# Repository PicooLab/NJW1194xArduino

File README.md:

# NJW1194 x Arduino

2-Channel Electronic Volume With Input Selector And Tone Control

Designed with Kicad and Arduino IDE;

## Related

+ NJW1194
  <https://www.njr.com/semicon/products/NJW1194.html>
  [Datasheet](assets/NJW1194_E.pdf)
+ Arduino Nano
  <https://store.arduino.cc/usa/arduino-nano>
+ 1602_I2C Screen
  <https://github.com/mathertel/LiquidCrystal_PCF8574>
+ EC11 Ratary Encoder
  <https://tech.alpsalpine.com/prod/e/html/encoder/incremental/ec11/ec11_list.html>

## Hardware

### 1. NJW1194 board

Size : 60mmx60mm

### 2. POWER board

Size : 60mmx60mm

### 3. CONTROL board

Size : 36mmx50mm

## Software

[Arduino nano](nano_eeprom_bal/nano_eeprom_bal.ino)

not elegant enough yet

## Assemble

TBD...

## MIT License

Copyright (c) 2020 ATRiiX

Permission is hereby granted, free of charge, to any person obtaining a copy
of this software and associated documentation files (the "Software"), to deal
in the Software without restriction, including without limitation the rights
to use, copy, modify, merge, publish, distribute, sublicense, and/or sell
copies of the Software, and to permit persons to whom the Software is
furnished to do so, subject to the following conditions:

The above copyright notice and this permission notice shall be included in all
copies or substantial portions of the Software.

THE SOFTWARE IS PROVIDED "AS IS", WITHOUT WARRANTY OF ANY KIND, EXPRESS OR
IMPLIED, INCLUDING BUT NOT LIMITED TO THE WARRANTIES OF MERCHANTABILITY,
FITNESS FOR A PARTICULAR PURPOSE AND NONINFRINGEMENT. IN NO EVENT SHALL THE
AUTHORS OR COPYRIGHT HOLDERS BE LIABLE FOR ANY CLAIM, DAMAGES OR OTHER
LIABILITY, WHETHER IN AN ACTION OF CONTRACT, TORT OR OTHERWISE, ARISING FROM,
OUT OF OR IN CONNECTION WITH THE SOFTWARE OR THE USE OR OTHER DEALINGS IN THE
SOFTWARE.

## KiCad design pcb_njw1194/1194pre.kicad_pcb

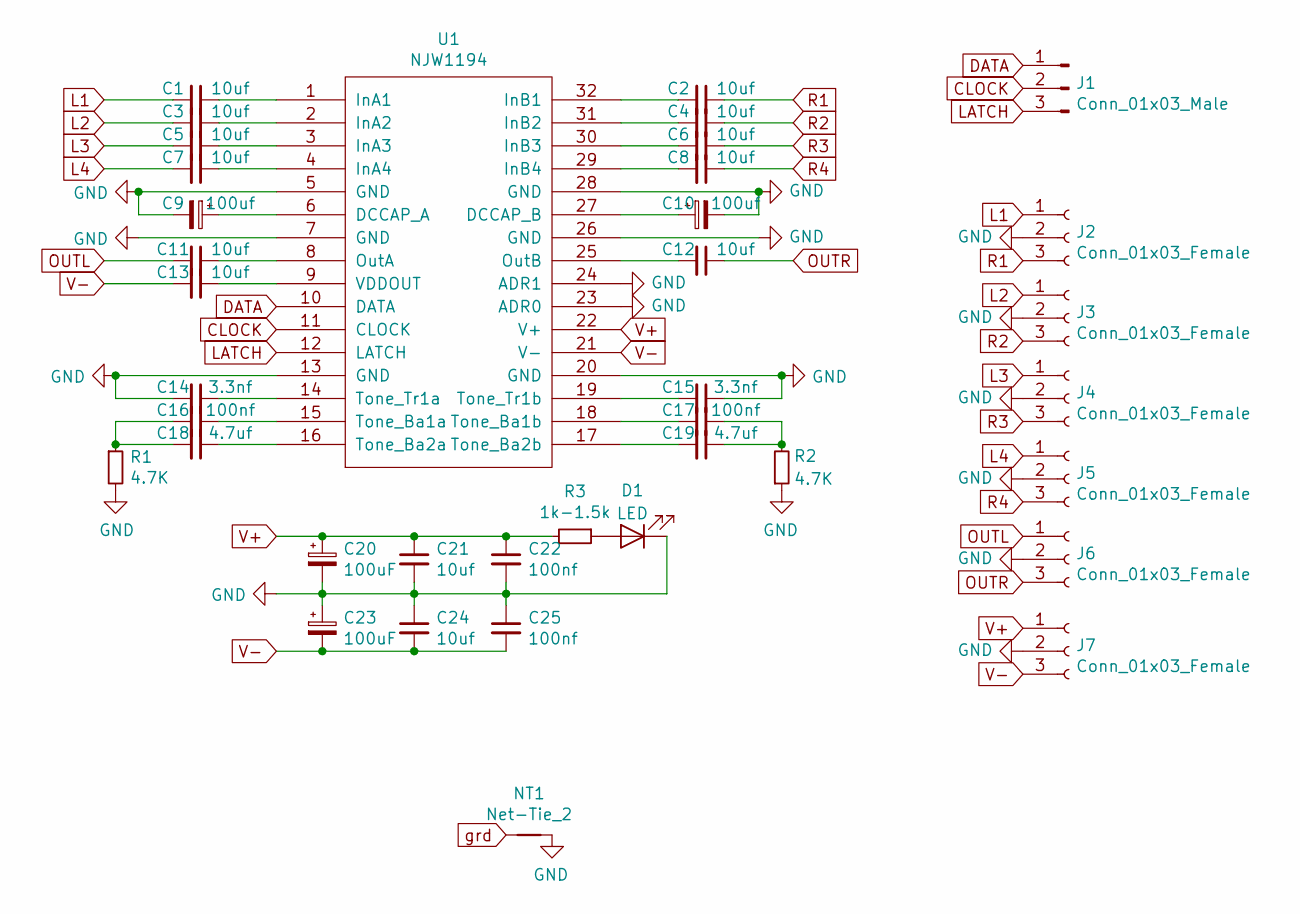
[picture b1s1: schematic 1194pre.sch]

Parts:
C1, C2, C3, C4, C5, C6, C7, C8, C11, C12, C13, C21, C24: 10uf; C_0805_2012Metric_Pad1.15x1.40mm_HandSolder
C9, C10: 100uf; CP_Radial_D8.0mm_P3.50mm
C14, C15: 3.3nf; C_0805_2012Metric_Pad1.15x1.40mm_HandSolder
C16, C17, C22, C25: 100nf; C_0603_1608Metric_Pad1.05x0.95mm_HandSolder
C18, C19: 4.7uf; C_0805_2012Metric_Pad1.15x1.40mm_HandSolder
C20, C23: 100uF; CP_Radial_D8.0mm_P3.50mm
D1: LED; LED_D3.0mm
J1: Conn_01x03_Male; PinHeader_1x03_P2.54mm_Vertical
J2, J3, J4, J5, J6, J7: Conn_01x03_Female; JST_XH_B3B-XH-A_1x03_P2.50mm_Vertical
NT1: Net-Tie_2; NetTie-2_SMD_Pad2.0mm
R1, R2: 4.7K; R_0805_2012Metric_Pad1.15x1.40mm_HandSolder
R3: 1k-1.5k; R_0805_2012Metric_Pad1.15x1.40mm_HandSolder
U1: NJW1194; TSSOP-32_6.1x11mm_P0.65mm

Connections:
CLOCK: J1.2, U1.11 (CLOCK)
DATA: J1.1, U1.10 (DATA)
GND: C9.2, C10.2, C14.2, C15.1, C20.2, C21.2, C22.2, C23.1, C24.1, C25.1, D1.1 (K), J2.2, J3.2, J4.2, J5.2, J6.2, J7.2, NT1.2, R1.2, R2.1, U1.5 (GND), U1.7 (GND), U1.13 (GND), U1.20 (GND), U1.23 (ADR0), U1.24 (ADR1), U1.26 (GND), U1.28 (GND)
L1: C1.2, J2.1
L2: C3.2, J3.1
L3: C5.2, J4.1
L4: C7.2, J5.1
LATCH: J1.3, U1.12 (LATCH)
unnamed: C1.1, U1.1 (InA1)
unnamed: C2.2, U1.32 (InB1)
unnamed: C3.1, U1.2 (InA2)
unnamed: C4.2, U1.31 (InB2)
unnamed: C5.1, U1.3 (InA3)
unnamed: C6.2, U1.30 (InB3)
unnamed: C7.1, U1.4 (InA4)
unnamed: C8.2, U1.29 (InB4)
unnamed: C9.1, U1.6 (DCCAP_A)
unnamed: C10.1, U1.27 (DCCAP_B)
unnamed: C11.1, U1.8 (OutA)
unnamed: C12.2, U1.25 (OutB)
unnamed: C13.1, U1.9 (VDDOUT)
unnamed: C14.1, U1.14 (Tone_Tr1a)
unnamed: C15.2, U1.19 (Tone_Tr1b)
unnamed: C16.1, U1.15 (Tone_Ba1a)
unnamed: C16.2, C18.2, R1.1
unnamed: C17.1, C19.1, R2.2
unnamed: C17.2, U1.18 (Tone_Ba1b)
unnamed: C18.1, U1.16 (Tone_Ba2a)
unnamed: C19.2, U1.17 (Tone_Ba2b)
unnamed: D1.2 (A), R3.1
OUTL: C11.2, J6.1
OUTR: C12.1, J6.3
R1: C2.1, J2.3
R2: C4.1, J3.3
R3: C6.1, J4.3
R4: C8.1, J5.3
V+: C20.1, C21.1, C22.1, J7.1, R3.2, U1.22 (V+)
V-: C13.2, C23.2, C24.2, C25.2, J7.3, U1.21 (V-)
grd: NT1.1

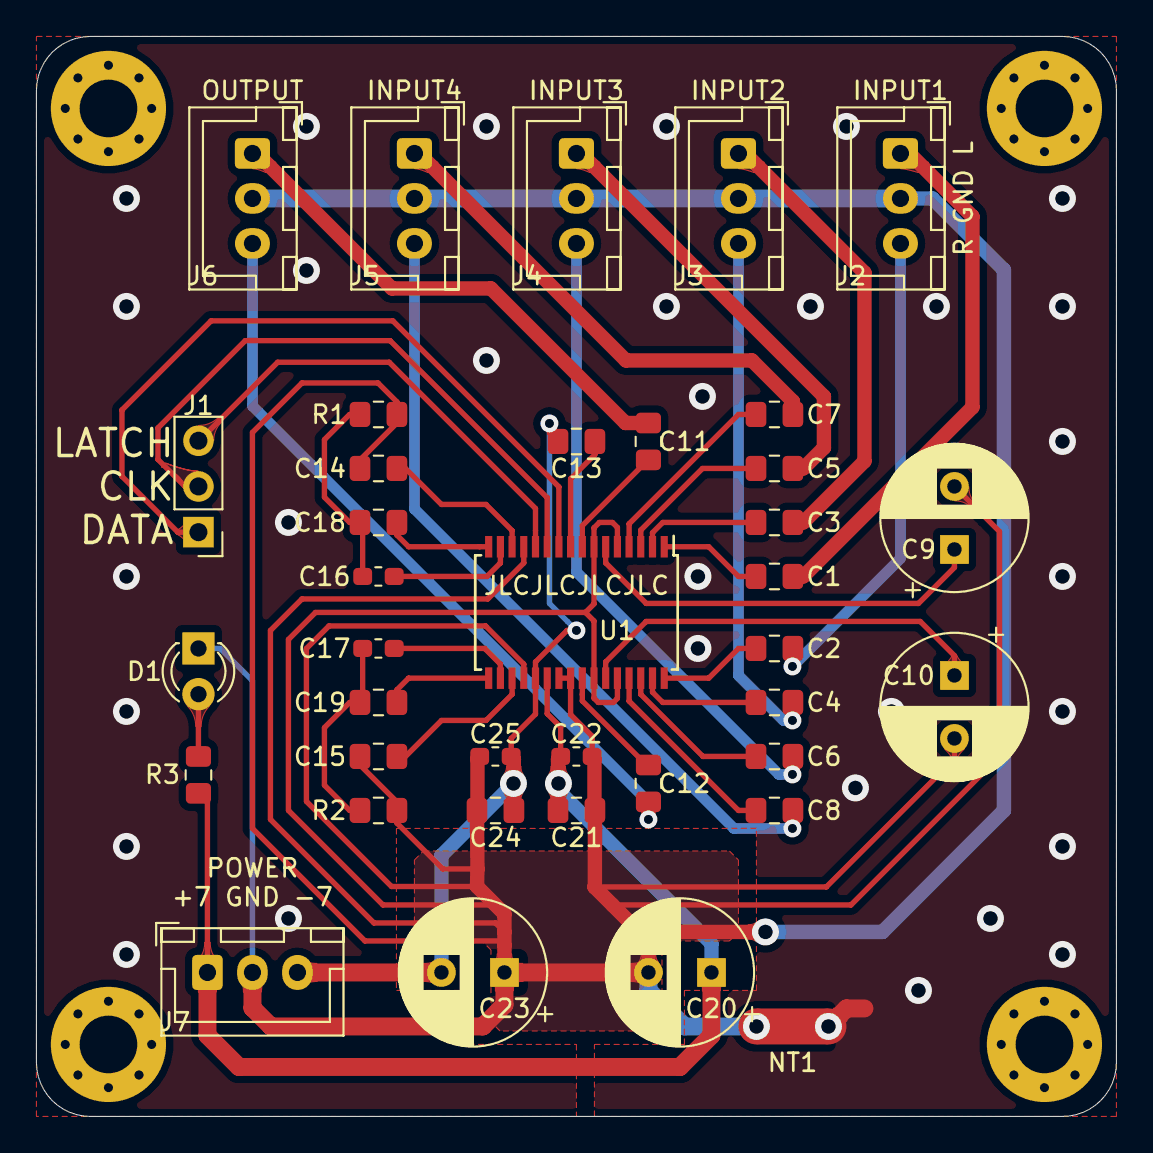
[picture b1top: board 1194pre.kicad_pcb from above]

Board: 2 copper layers, 60.0 x 60.0 mm, 38 parts (0 on the bottom side), 38 nets.

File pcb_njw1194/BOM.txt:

BOM of NJW1194

J1;                   PinHeader_P2.54mm_3P;   1;
J2-J7;                JST_XH2.54mm_3P;        6;

U1;                   SSOP-32;                1;    NJW1194;

R1,R2;                R_0805;                 2;    4.7K;
R3;                   R_0805;                 1;    1k-1.5k;
D1;                   LED_D3.0mm;             1;

C9,C10,C20,C23;       CP_D8mm_P3.5mm;         2;    100uF;
C16,C17,C22,C25;      C_0603";                4;    100nf;
C1-C8,C11-13,C21,C24; C_0805";               13;    10uf;
C14,C15;              C_0805";                2;    3.3nf;
C18,C19;              C_0805";                2;    4.7uf;

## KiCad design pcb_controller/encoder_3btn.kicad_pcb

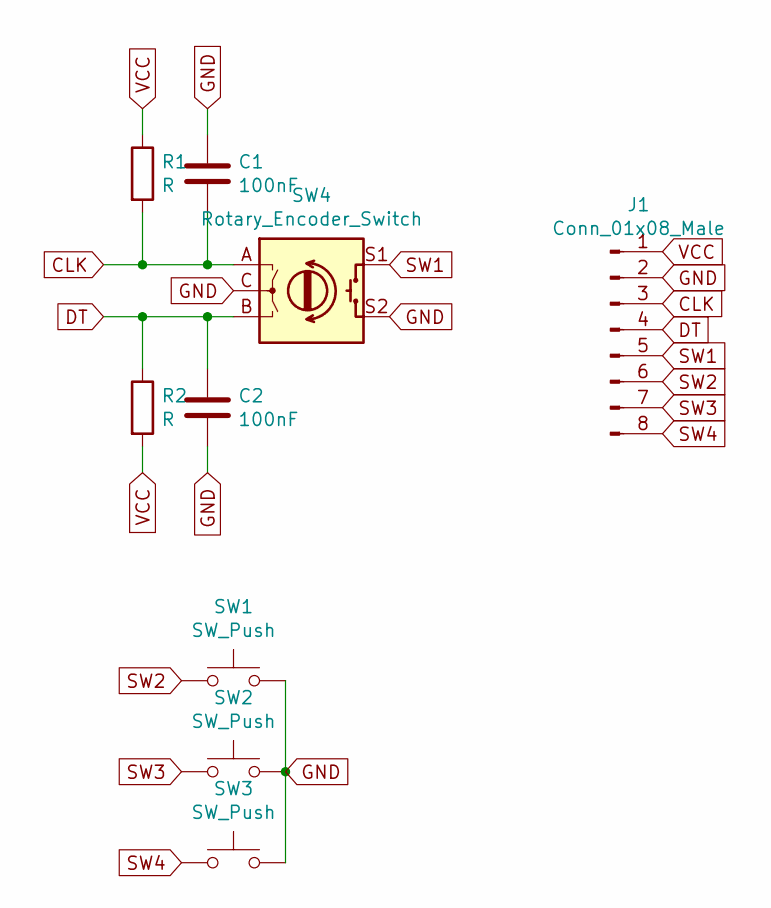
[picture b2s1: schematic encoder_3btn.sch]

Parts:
C1, C2: 100nF; C_0603_1608Metric_Pad1.05x0.95mm_HandSolder
J1: Conn_01x08_Male; PinHeader_1x08_P2.54mm_Horizontal
R1, R2: R; R_0805_2012Metric_Pad1.15x1.40mm_HandSolder
SW1, SW2, SW3: SW_Push; SW_PUSH_6mm_H13mm
SW4: Rotary_Encoder_Switch; RotaryEncoder_Alps_EC11E-Switch_Vertical_H20mm

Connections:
CLK: C1.2, J1.3, R1.2, SW4.A
DT: C2.1, J1.4, R2.1, SW4.B
GND: C1.1, C2.2, J1.2, SW1.2, SW2.2, SW3.2, SW4.C, SW4.S2
SW1: J1.5, SW4.S1
SW2: J1.6, SW1.1
SW3: J1.7, SW2.1
SW4: J1.8, SW3.1
VCC: J1.1, R1.1, R2.2

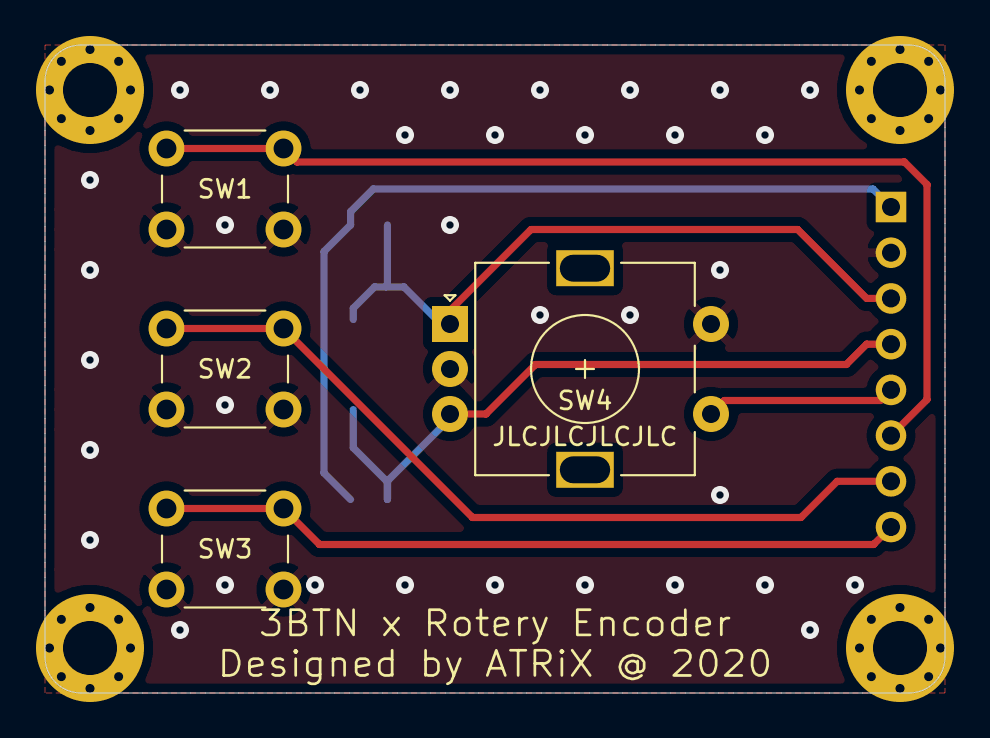
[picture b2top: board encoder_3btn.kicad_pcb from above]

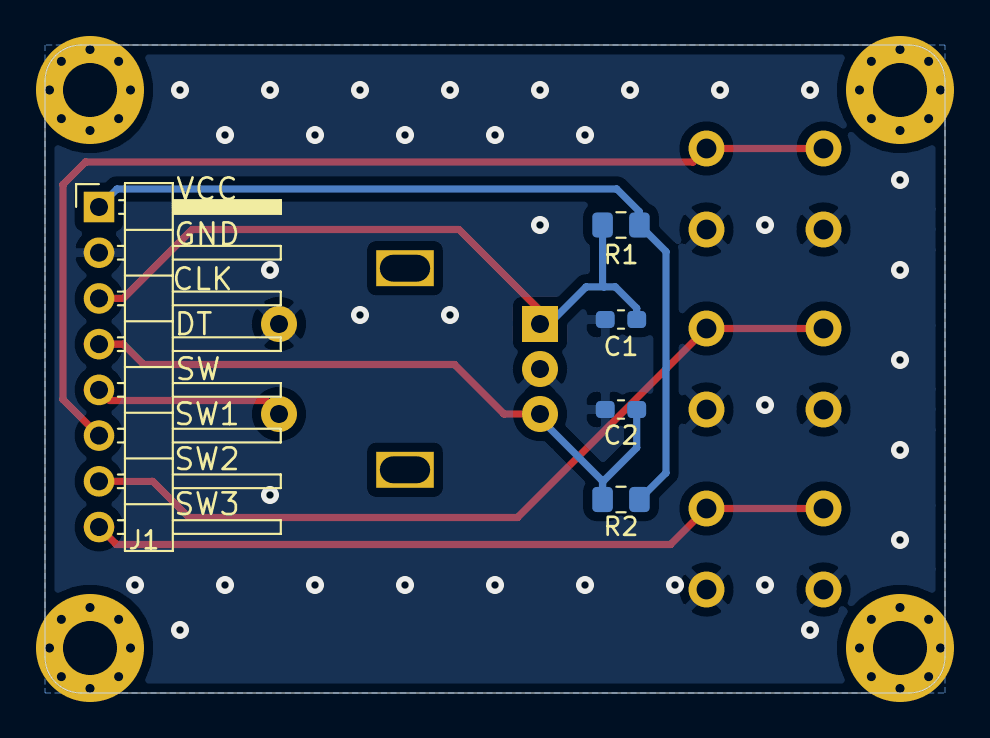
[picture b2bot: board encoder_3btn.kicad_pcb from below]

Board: 2 copper layers, 50.0 x 36.0 mm, 13 parts (5 on the bottom side), 8 nets.

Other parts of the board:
REF1, REF2, REF3, REF4: MountingHole_3mm_Pad_Via

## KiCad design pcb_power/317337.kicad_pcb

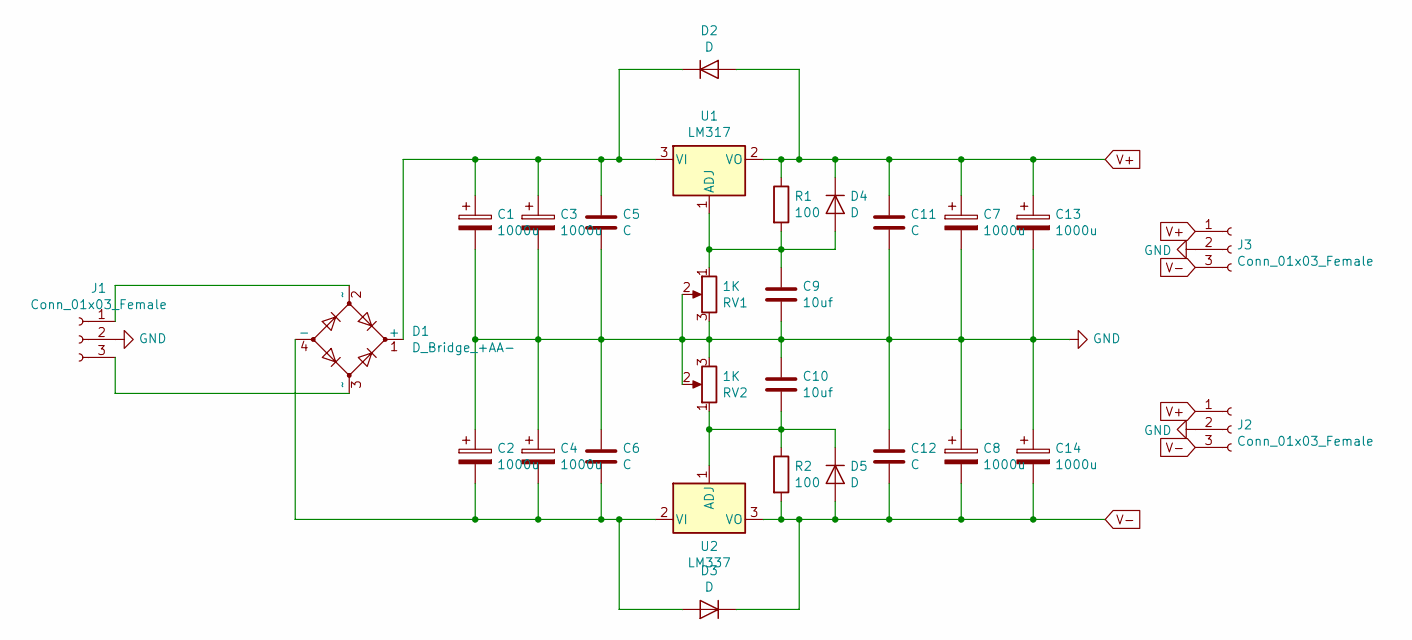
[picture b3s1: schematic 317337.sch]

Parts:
C1, C2, C3, C4, C7, C8, C13, C14: 1000u; CP_Radial_D10.0mm_P5.00mm
C5, C6, C11, C12: C; C_0603_1608Metric_Pad1.05x0.95mm_HandSolder
C9, C10: 10uf; C_0805_2012Metric_Pad1.15x1.40mm_HandSolder
D1: D_Bridge_+AA-; Diode_Bridge_Vishay_GBL
D2, D3, D4, D5: D; D_A-405_P7.62mm_Horizontal
J1: Conn_01x03_Female; PhoenixContact_MSTBVA_2,5_3-G-5,08_1x03_P5.08mm_Vertical
J2, J3: Conn_01x03_Female; JST_XH_B3B-XH-A_1x03_P2.50mm_Vertical
R1, R2: 100; R_Axial_DIN0207_L6.3mm_D2.5mm_P10.16mm_Horizontal
RV1, RV2: 1K; Potentiometer_Bourns_3296W_Vertical
U1: LM317; TO-220-3_Vertical
U2: LM337; TO-220-3_Vertical

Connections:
GND: C1.2, C2.1, C3.2, C4.1, C5.2, C6.1, C7.2, C8.1, C9.2, C10.1, C11.2, C12.1, C13.2, C14.1, J1.2, J2.2, J3.2, RV1.2, RV1.3, RV2.2, RV2.3
unnamed: C1.1, C3.1, C5.1, D1.1 (+), D2.1 (K), U1.3 (VI)
unnamed: C2.2, C4.2, C6.2, D1.4 (-), D3.2 (A), U2.2 (VI)
unnamed: C9.1, D4.2 (A), R1.2, RV1.1, U1.1 (ADJ)
unnamed: C10.2, D5.1 (K), R2.1, RV2.1, U2.1 (ADJ)
unnamed: D1.2 (~~), J1.1
unnamed: D1.3 (~~), J1.3
V+: C7.1, C11.1, C13.1, D2.2 (A), D4.1 (K), J2.1, J3.1, R1.1, U1.2 (VO)
V-: C8.2, C12.2, C14.2, D3.1 (K), D5.2 (A), J2.3, J3.3, R2.2, U2.3 (VO)

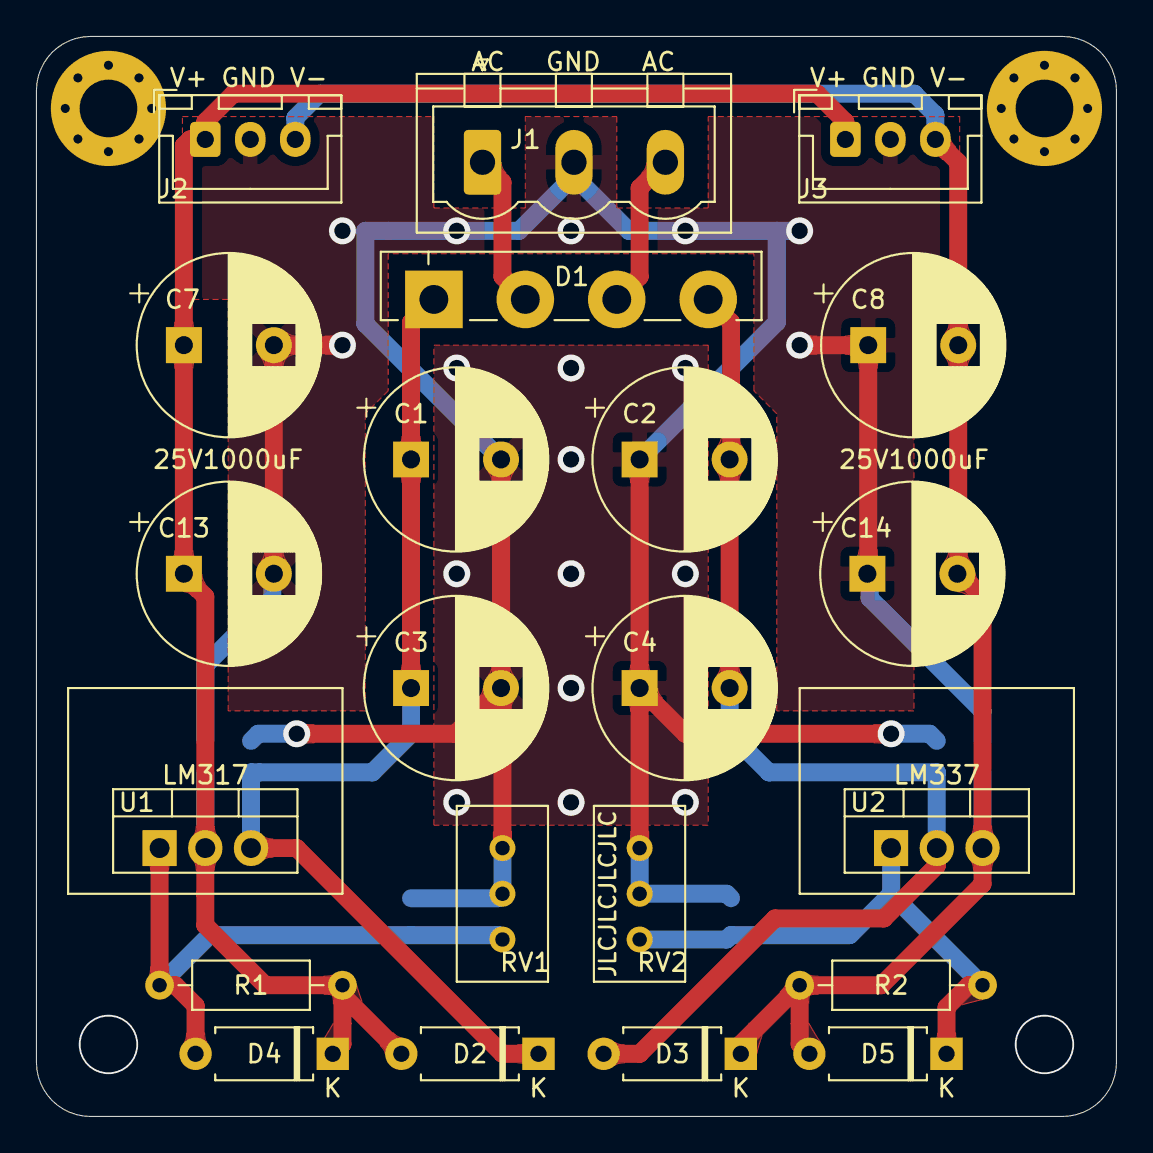
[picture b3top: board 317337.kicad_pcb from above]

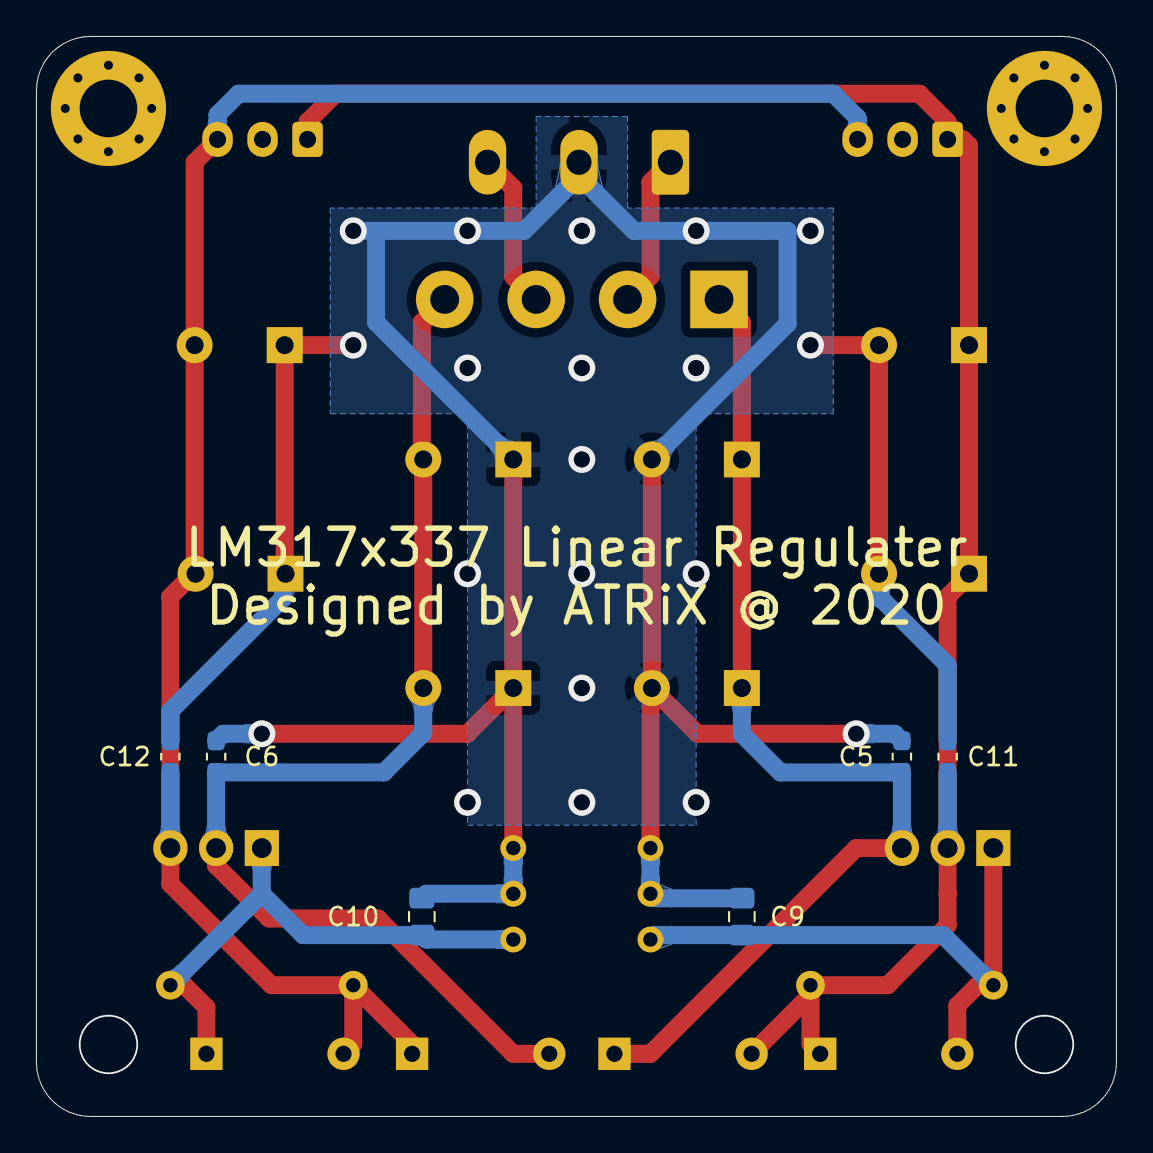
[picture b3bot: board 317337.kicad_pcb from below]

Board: 2 copper layers, 60.0 x 60.0 mm, 28 parts (6 on the bottom side), 9 nets.

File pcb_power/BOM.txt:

BOM of LM317x337

J1;                  "5.08mm_3P";        1;
J2,J3;               "XH2.54_3P";        2;

U1;                  "TO-220";           1;    LM317;
U2;                  "TO-220";           1;    LM337;

R1,R2;               "R1/4W";            2;    100;
RV2,RV1;             "3296W";            2;    1K;
D1";                 "Diode_Bridge";     1;    D_Bridge_+AA-;
D2-D5;               "4N7001";           4;

C14,C13,C8,C7,C1-C4; "CP_D10mm_P5mm";    8;    1000u;
C12,C11,C6,C5;       "C_0603;            4;    100nf
C10,C9;              "C_0805";           2;    10uf;

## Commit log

2020-04-18 rev.a
